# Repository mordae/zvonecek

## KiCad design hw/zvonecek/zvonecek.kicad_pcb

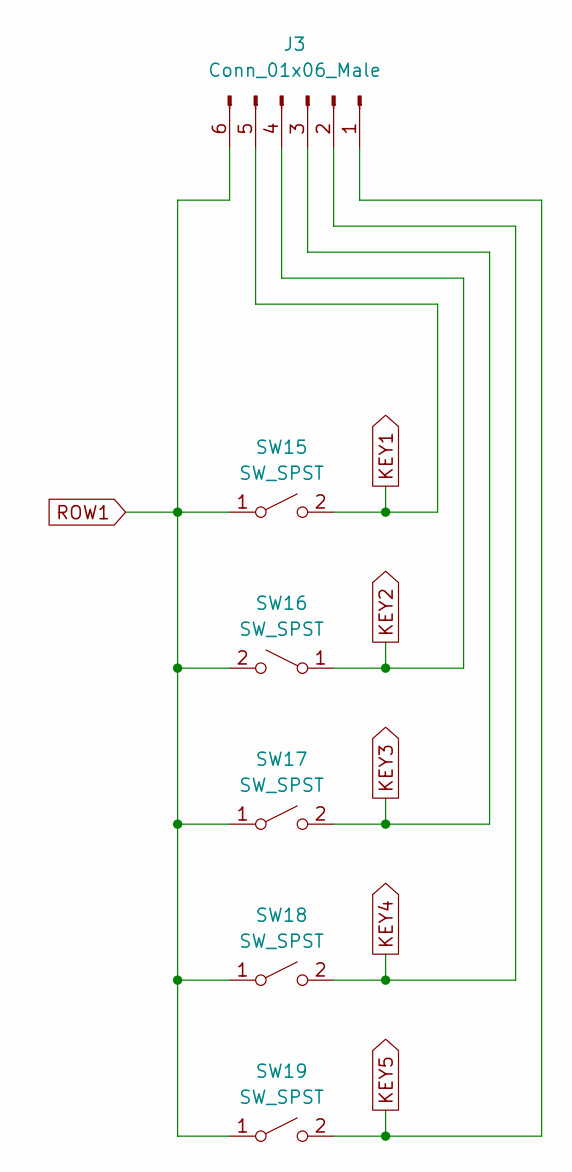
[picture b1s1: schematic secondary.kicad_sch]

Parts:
J3: Conn_01x06_Male; PinHeader_1x06_P2.54mm_Vertical
SW15, SW16, SW17, SW18, SW19: SW_SPST; BUTTON

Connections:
KEY1: J3.5, SW15.2 (B); also elsewhere on the board
KEY2: J3.4, SW16.1 (A); also elsewhere on the board
KEY3: J3.3, SW17.2 (B); also elsewhere on the board
KEY4: J3.2, SW18.2 (B); also elsewhere on the board
KEY5: J3.1, SW19.2 (B); also elsewhere on the board
ROW1: J3.6, SW15.1 (A), SW16.2 (B), SW17.1 (A), SW18.1 (A), SW19.1 (A); also elsewhere on the board

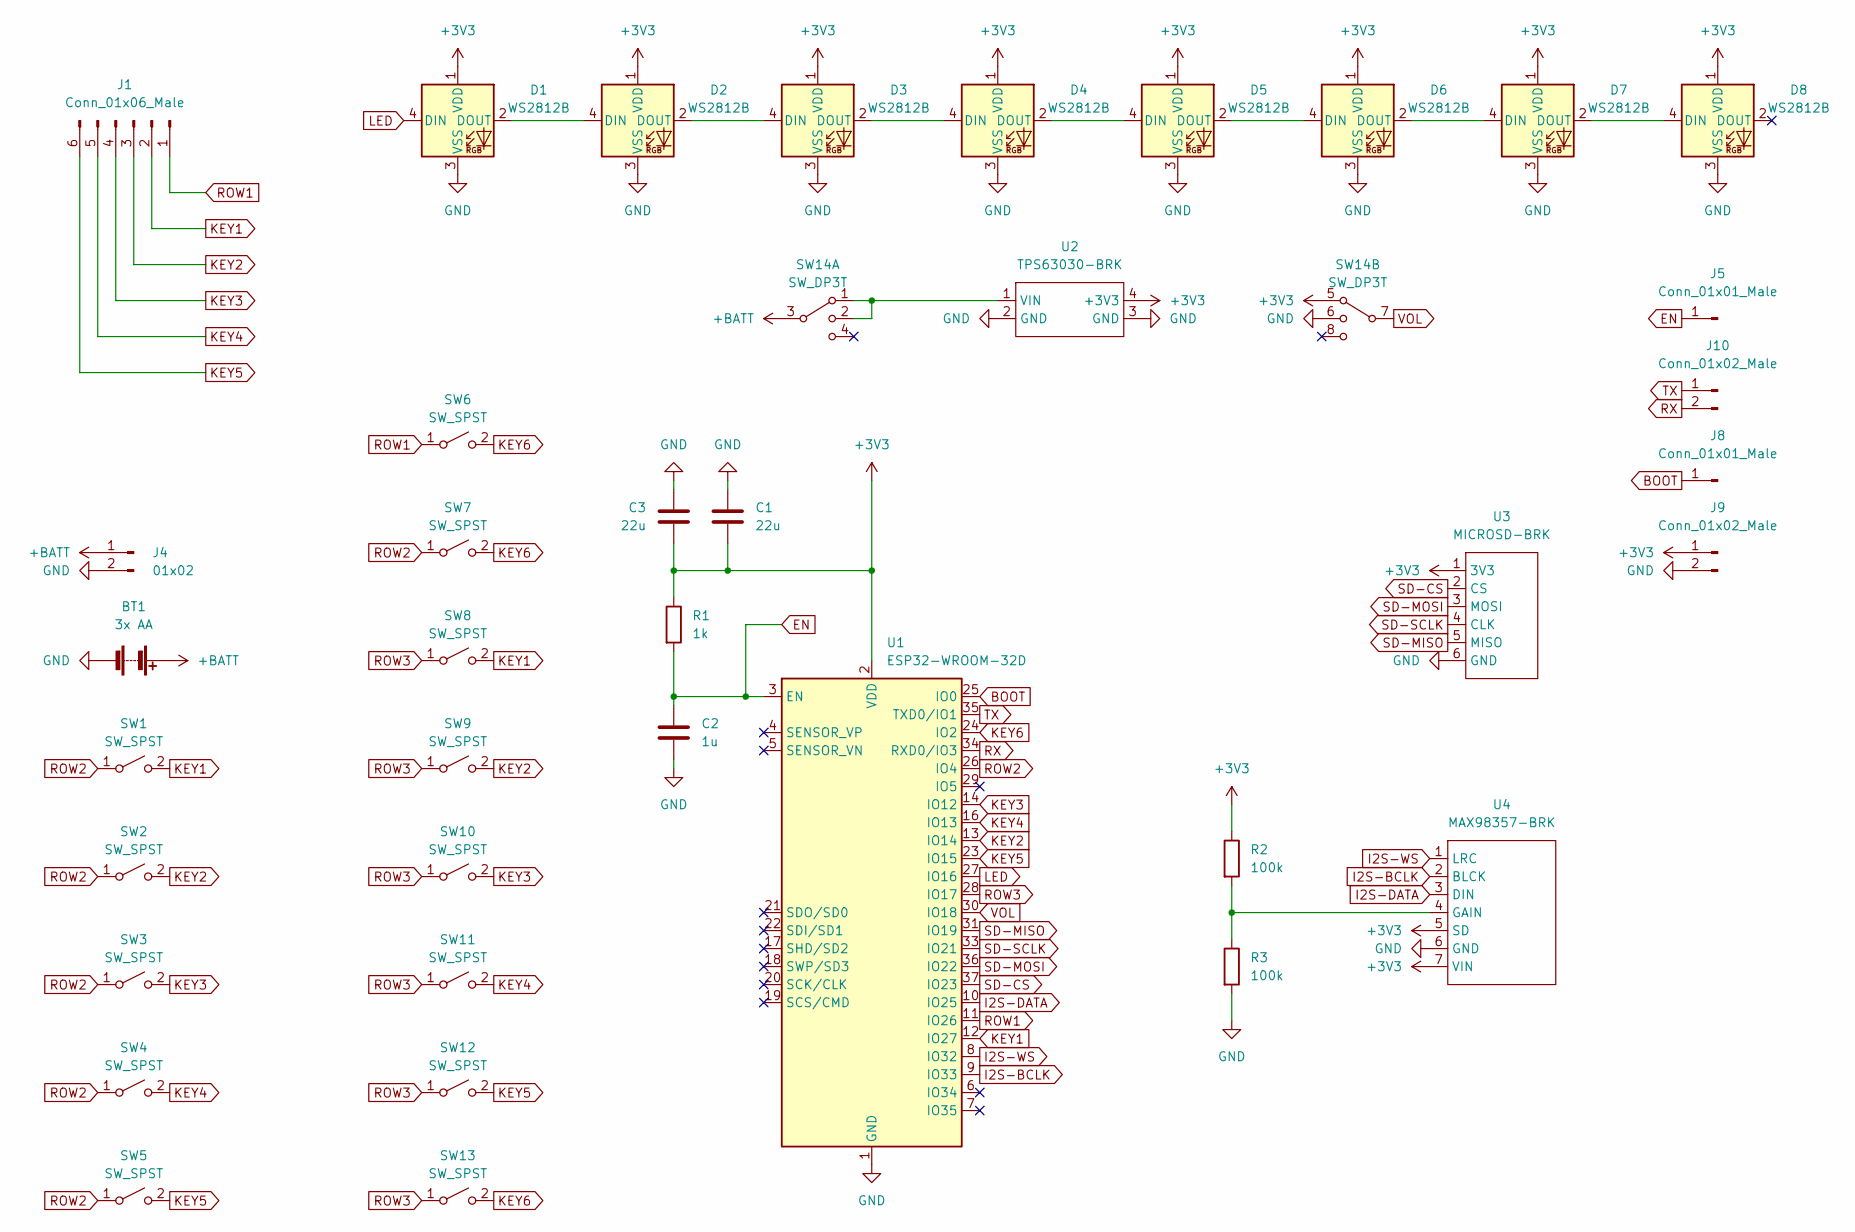
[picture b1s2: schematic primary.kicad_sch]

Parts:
BT1: 3x AA; PinHeader_1x02_P2.54mm_Horizontal
C1, C3: 22u; C_0603_1608Metric
C2: 1u; C_0805_2012Metric
D1, D2, D3, D4, D5, D6, D7, D8: WS2812B; LED_WS2812B_PLCC4_5.0x5.0mm_P3.2mm
J1: Conn_01x06_Male; PinHeader_1x06_P2.54mm_Vertical
J4: 01x02; PinHeader_1x02_P2.54mm_Vertical
J5, J8: Conn_01x01_Male; PinHeader_1x01_P2.54mm_Vertical
J9, J10: Conn_01x02_Male; PinHeader_1x02_P2.54mm_Vertical
R1: 1k; R_0603_1608Metric
R2, R3: 100k; R_0603_1608Metric
SW1, SW2, SW3, SW4, SW5, SW6, SW7, SW8, SW9, SW10, SW11, SW12, SW13: SW_SPST; BUTTON
SW14: SW_DP3T; SWITCH
U1: ESP32-WROOM-32D; ESP32-WROOM-32
U2: TPS63030-BRK
U3: MICROSD-BRK
U4: MAX98357-BRK

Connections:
+3V3: C1.2, C3.2, D1.1 (VDD), D2.1 (VDD), D3.1 (VDD), D4.1 (VDD), D5.1 (VDD), D6.1 (VDD), D7.1 (VDD), D8.1 (VDD), J9.1, R1.1, R2.1, SW14.5, U1.2 (VDD), U2.4 (+3V3), U3.1 (3V3), U4.5 (SD), U4.7 (VIN)
+BATT: BT1.1 (+), J4.1, SW14.3
BOOT: J8.1, U1.25 (IO0)
EN: C2.1, J5.1, R1.2, U1.3 (EN)
GND: BT1.2 (-), C1.1, C2.2, C3.1, D1.3 (VSS), D2.3 (VSS), D3.3 (VSS), D4.3 (VSS), D5.3 (VSS), D6.3 (VSS), D7.3 (VSS), D8.3 (VSS), J4.2, J9.2, R3.2, SW14.6, U1.1 (GND), U1.15 (GND), U1.38 (GND), U1.39 (GND), U2.2 (GND), U2.3 (GND), U3.6 (GND), U4.6 (GND)
I2S-BCLK: U1.9 (IO33), U4.2 (BLCK)
I2S-DATA: U1.10 (IO25), U4.3 (DIN)
I2S-WS: U1.8 (IO32), U4.1 (LRC)
KEY1: J1.2, SW1.2 (B), SW8.2 (B), U1.12 (IO27); also elsewhere on the board
KEY2: J1.3, SW2.2 (B), SW9.2 (B), U1.13 (IO14); also elsewhere on the board
KEY3: J1.4, SW3.2 (B), SW10.2 (B), U1.14 (IO12); also elsewhere on the board
KEY4: J1.5, SW4.2 (B), SW11.2 (B), U1.16 (IO13); also elsewhere on the board
KEY5: J1.6, SW5.2 (B), SW12.2 (B), U1.23 (IO15); also elsewhere on the board
KEY6: SW6.2 (B), SW7.2 (B), SW13.2 (B), U1.24 (IO2)
LED: D1.4 (DIN), U1.27 (IO16)
unnamed: D1.2 (DOUT), D2.4 (DIN)
unnamed: D2.2 (DOUT), D3.4 (DIN)
unnamed: D3.2 (DOUT), D4.4 (DIN)
unnamed: D4.2 (DOUT), D5.4 (DIN)
unnamed: D5.2 (DOUT), D6.4 (DIN)
unnamed: D6.2 (DOUT), D7.4 (DIN)
unnamed: D7.2 (DOUT), D8.4 (DIN)
unnamed: SW14.1, SW14.2, U2.1 (VIN)
unnamed: R2.2, R3.1, U4.4 (GAIN)
ROW1: J1.1, SW6.1 (A), U1.11 (IO26); also elsewhere on the board
ROW2: SW1.1 (A), SW2.1 (A), SW3.1 (A), SW4.1 (A), SW5.1 (A), SW7.1 (A), U1.26 (IO4)
ROW3: SW8.1 (A), SW9.1 (A), SW10.1 (A), SW11.1 (A), SW12.1 (A), SW13.1 (A), U1.28 (IO17)
RX: J10.2, U1.34 (RXD0/IO3)
SD-CS: U1.37 (IO23), U3.2 (CS)
SD-MISO: U1.31 (IO19), U3.5 (MISO)
SD-MOSI: U1.36 (IO22), U3.3 (MOSI)
SD-SCLK: U1.33 (IO21), U3.4 (CLK)
TX: J10.1, U1.35 (TXD0/IO1)
VOL: SW14.7, U1.30 (IO18)

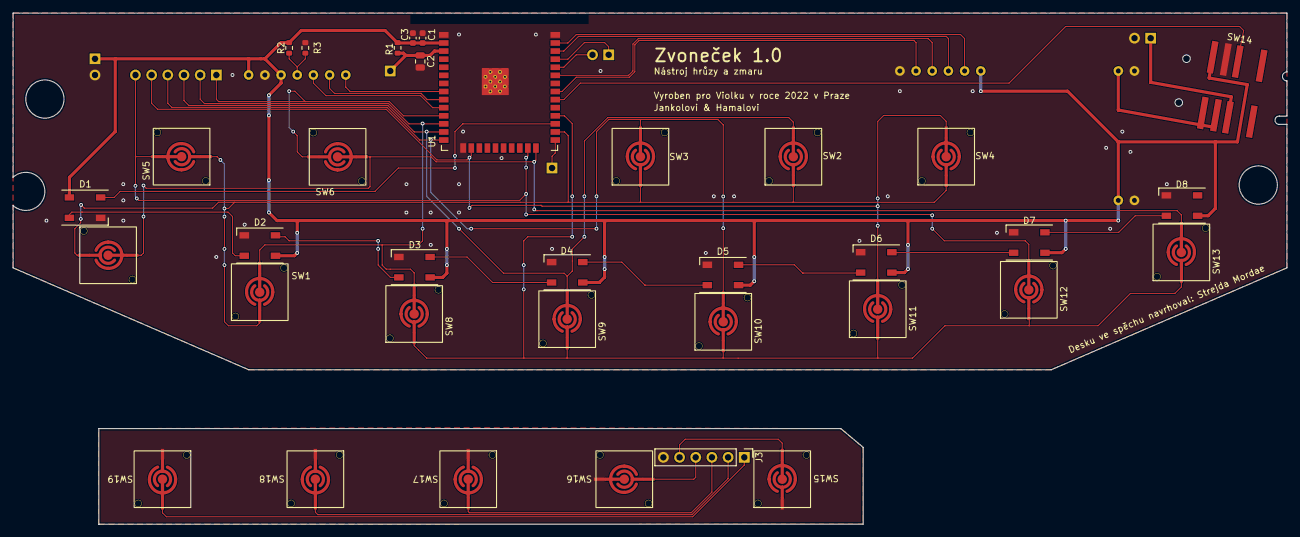
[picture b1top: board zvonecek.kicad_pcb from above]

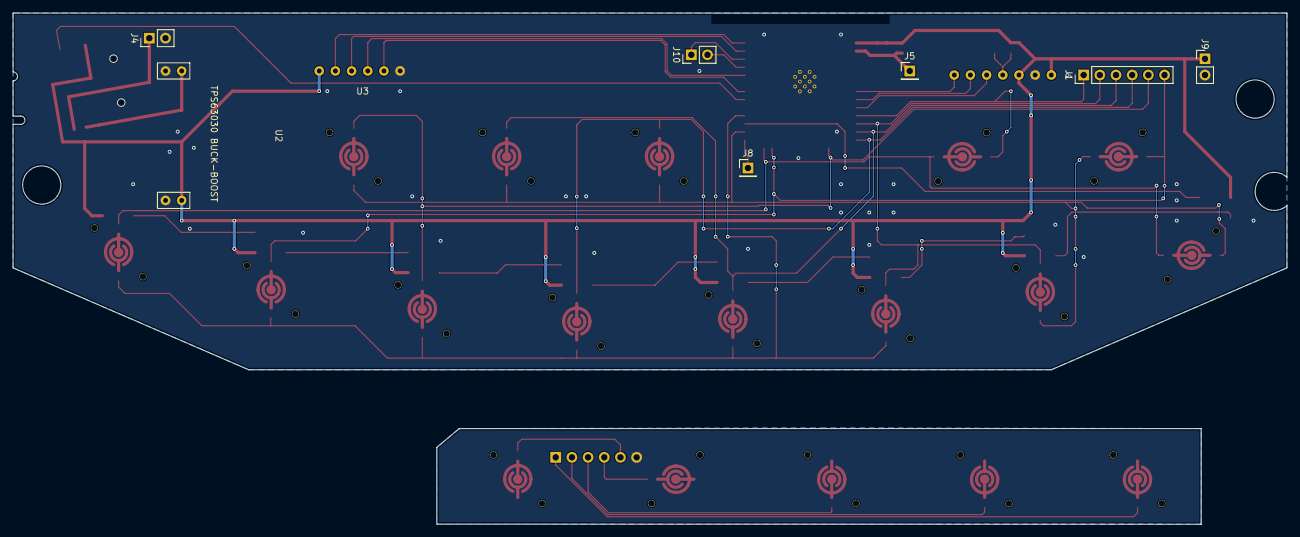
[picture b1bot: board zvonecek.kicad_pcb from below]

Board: 2 copper layers, 200.0 x 80.3 mm, 44 parts (9 on the bottom side), 34 nets.

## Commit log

2022-10-23 Add WIP hardware design
2022-12-20 HW design 1.0 as manufactured
2022-12-20 Start work on I/O
2022-12-21 Emit pure tones for now
2022-12-21 Introduce string synthesis
2022-12-22 Fix string frequencies
2022-12-22 Minor clean up and small improvements
2022-12-22 We have 4M flash
2022-12-22 Fix simultaneous key presses and holding
2022-12-22 Prevent most troublesome multi-key errors
2022-12-22 Add two more songs and use leds for highlight
2022-12-23 Seed random number generator at startup
2022-12-23 Add startup song
2022-12-23 Make LEDs brighter
2022-12-24 Clean up and break code into scenes
2022-12-25 Run at 240MHz by default
2022-12-25 Get rid of strength setting
2022-12-25 Utilize full volume range
2022-12-25 Remove volume ducking for now
2022-12-25 Resolve most of the issues, add final song
2022-12-25 Suspend RMT when not controlling LEDs
2022-12-25 Enable light sleep to save power
2022-12-25 Implement idle warning
2022-12-26 Move idle repeat interval to menuconfig
2022-12-26 Comment keyboard static variables
2022-12-26 Implement menu, empty for now
2022-12-26 Implement volume control and instrument disable
2022-12-28 Add data partition
2022-12-28 Abstract strings to instruments
2022-12-28 Always play all strings
2022-12-28 Limit number of simultaneous keys to 2
2022-12-28 Implement special sounds
